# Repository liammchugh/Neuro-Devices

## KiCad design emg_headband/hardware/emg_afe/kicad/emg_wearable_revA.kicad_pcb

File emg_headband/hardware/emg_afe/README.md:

# EMG wearable, Rev A (KiCad, JLCPCB)

One to three channel surface EMG front end on a battery-powered headband
wearable, built around a TI ADS1298 and an ESP32-S3-MINI-1 module (placed by
JLCPCB, no hand soldering) that sends data to the
pedal wirelessly. The original discrete single-channel design (INA333 + OPA2333)
is in git history (commit 3aedaac) and in `../../docs/`.

Rev A is a bench board. Synthetic differential inputs first; no body electrodes
until the isolation checks in "Bring-up" pass.

## Requirements (reviewed, Liam, 11 Oct 2026)

1. Works with 1, 2 or 3 simultaneous electrode pairs, chosen by firmware mode,
   with no rework.
2. Electrodes: one 3.5 mm TRS jack for CH1 (tip +, ring −, sleeve REF) plus a
   1 mm FPC carrying CH1 to CH3 for flex-PCB arrays or a breakout (Liam, 11 Oct
   2026: three 3.5 mm jacks do not fit the 2.5" × 1" board). All REF sleeves share
   one reference/RLD net, so 9 electrodes (3 REF) or 7 (1 REF) both work.
   Series resistors on every input.
3. Power: passive USB/battery handling in every state (battery, USB, both), no
   switches. Dedicated low-noise analog rail. Protected LiPo.
4. Debug: USB serial over the board USB-C (ESP32-S3 native USB). The isolated UART footprint was
   dropped for size.
9. Board: 2-layer flex PCB, 62.5 × 25.4 mm (2.46" × 1"; limit 2.5" × 1"),
   ESP32-S3 module at one end with USB-C pointing down (across the long axis),
   jack and FPC at the other end. Everything JLC-assembled (Liam, 11 Oct 2026:
   chip on board instead of a XIAO, whose BAT pads are on its underside).
5. Filtering in firmware: capture wide (about 0.5 Hz up, 4 kSPS or more) so
   blink/EOG and envelope data are kept; 20 to 450 Hz is the EMG band.
6. Lead-off detection (built into the ADS1298).
7. JLCPCB assembly, LCSC parts, smallest practical size for a headband.
8. Pedal side is out of scope; it gets data wirelessly.

## Decisions

| Topic | Decision | Source |
|---|---|---|
| Architecture | Battery wearable, wireless to pedal (BLE / ESP-NOW). USB-C for flashing, charging and serial debug | Liam, 11 Oct 2026 |
| Front end | ADS1298 (8 ch, 24-bit, PGA, RLD, lead-off), CH1 to CH3 used, CH4 to CH8 tied to AVDD and powered down | Liam, 11 Oct 2026 |
| Sample rate | 4 kSPS (or 8 kSPS) from the ADS1298, decimate in firmware | Reviews |
| Filtering | Firmware: HPF about 0.5 Hz for wideband capture, 20 to 450 Hz for EMG features | Liam, 11 Oct 2026 |
| Input network | 22 kΩ series + 100 pF C0G to AGND per input (≈ 72 kHz; kept small for dry-electrode CMRR). The ADS1298 modulator runs at 512 kHz, so no higher-order anti-alias filter is needed | Datasheet |
| Reference / RLD | RLDOUT with 1 MΩ ∥ 1.5 nF feedback (datasheet), 330 kΩ series to the REF electrode(s), DC fault current < 10 µA | Datasheet, critic review |
| Schematic | Flat, one A3 sheet | Review 2 |

## Isolation and USB debug

The wearable is isolated from the pedal and mains by being battery powered and
wireless. The USB-C port is the one non-isolated path: when it is plugged
into a computer, the body would be connected through the reference electrode,
AGND and the USB shield to mains earth, and the guitar strings are on mains
earth too.

Rev A relies on one rule: **USB serial over the board's USB-C is the debug
path** (Liam, 11 Oct 2026), as on any Arduino-style R&D board. With electrodes
on the body and USB plugged in, run the laptop on battery and unplugged from
mains, or use a synthetic input instead of electrodes. This note is on the
schematic. A USB isolator dongle between the laptop and the board is the easy
upgrade when the laptop has to stay on mains.

The isolated UART footprint (ISO7721) from earlier drafts was dropped to fit
the 2.5" × 1" flex board.

Charging while worn: only from a battery-powered laptop or an isolated (Class II) USB charger.

## Circuit

**Power and reference**
- LiPo (protected cell) soldered to J3 (two SMD pads next to the USB-C).
  U8 MCP73831 charges it from USB at 100 mA (R703 = 10 kΩ; lower R703 for a
  bigger cell).
- Passive power path, no switches: USB 5 V through a Schottky (D101, B5819W)
  and the battery through a P-MOSFET (Q101, AO3401A, gate on VBUS with a 100 kΩ
  pull-down) join at `VSYS`. USB present: Q101 is off and VSYS ≈ 4.7 V from
  USB. USB absent: Q101 is on and VSYS = VBAT. Both: USB carries the load while
  U8 charges the battery.
- **On/off:** SW1 (MSK12C02 side slide switch, lever out of the bottom edge
  next to the filter block) sits between the battery and Q101. Off: the cell
  is fully disconnected from the system (0 µA); USB still powers the board and
  U8 still charges the cell. Slide toward the "ON" label to turn it on.
- **Battery monitor:** VBAT_SYS / 2 (1 MΩ / 1 MΩ, 100 nF) into IO10
  (ADC1_CH9); draws 2 µA only while on.
- **Charge LED:** D102 (red) from VBUS through 1 kΩ into the MCP73831 STAT
  pin; lit while charging, off when full or without USB.
- `+3V3` (ESP32-S3, ADS1298 DVDD) from U9 AP2112K-3.3 (600 mA) on VSYS.
- `+3V0_A` (ADS1298 AVDD) from a dedicated low-noise LDO (U6, LP5907MFX-3.0,
  6.5 µVrms, 82 dB PSRR at 1 kHz) on VSYS. EN is tied to `+3V3`, so the AFE is
  never live while the MCU rail is off. AVDD − DVDD = −0.3 V, inside the −2.1
  to 3.6 V limit.

**MCU and USB**
- U2 ESP32-S3-MINI-1-N8 (8 MB flash, PCB antenna at the board end; the
  antenna area is kept free of copper on both layers).
- J7 HRO TYPE-C-31-M-12 USB-C (5.1 kΩ CC pull-downs), USBLC6-2SC6 ESD, data
  to the ESP32-S3 native USB (IO19/IO20). Flashing and serial go through the
  built-in USB-Serial-JTAG, so no USB-UART chip or auto-reset circuit.
- EN: 10 kΩ / 1 µF RC. No buttons, to save space: if USB ever stops
  enumerating, short TP10 (IO0) to GND and tap TP9 (EN) to GND to force the
  ROM bootloader. Both pads are on the back.

**Electrodes**
- J1: CUI SJ-3523-SMT 3.5 mm TRS jack for CH1 (tip ELEC1_P, ring ELEC1_N,
  sleeve `RLD_ELEC`).
- J6: Hirose FH34SRJ-12S-0.5SH(50) back-flip FPC (C424659; 12 pins, 0.5 mm,
  1.0 mm tall), in parallel with J1 for CH1: use one or the other. CH2 and CH3 are on J6 only. Pinout: 1 AGND, 2/3 CH1 P/N, 4 REF, 5 AGND, 6/7 CH2 P/N, 8 REF, 9 AGND,
  10/11 CH3 P/N, 12 REF, MP AGND. Footprint `emg_wearable:Hirose_FH34SRJ-12S-0.5SH_...` is drawn from
  the Hirose land pattern; check it against the datasheet before ordering. The
  FPC inserts from the mounting-tab side, which faces the board edge; the
  signal pads and back-flip actuator are on the inboard side.

**ADS1298 (U1)**
- IN1 to IN3 from the input RC (22 kΩ + 100 pF C0G). IN4 to IN8 and TESTP_PACE_OUT1/2 to AVDD, as
  the datasheet asks for unused analog pins.
- Internal 2.4 V reference: VREFP 10 µF + 100 nF to AGND, VREFN to AGND.
- VCAP1 22 µF, VCAP2/3/4 1 µF to AGND. AVDD 10 µF + 2× 100 nF, DVDD 1 µF +
  100 nF.
- Internal clock (CLKSEL high, CLK not connected). RESV1 and DAISY_IN to DGND.
  RLDREF and WCT not connected (internal mid-supply reference). GPIO1 to 4 not
  connected: set them as outputs in firmware.
- RLDIN tied to `RLD_ELEC` so firmware can measure the REF electrode.
- SPI to the ESP32-S3: IO12 SCLK, IO13 DOUT (MISO), IO14 DIN (MOSI), IO15 CS
  (10 k pull-up), IO16 DRDY, IO17 START, IO18 RESET (10 k pull-up). PWDN held
  high by 10 k; use register standby instead. Strapping pins (IO0, IO3, IO45,
  IO46) are not used.
- Firmware: power down unused channels (CHnSET.PDn), pick RLD sense channels
  (RLD_SENSP/N) and use lead-off (LOFF) to detect which electrodes are attached.

## BOM notes for JLCPCB

| Part | LCSC | Note |
|---|---|---|
| ADS1298IPAGR | C527440 | extended, ≈ $20, 1,953 in stock on 11 Oct 2026 |
| LP5907MFX-3.0/NOPB | C475492 | extended |
| ESP32-S3-MINI-1-N8 | C2913206 | extended, footprint from the CERN library (CERN-OHL-P-2.0) |
| TYPE-C-31-M-12 | C165948 | extended, has through-hole shell tabs |
| MCP73831T-2ACI/OT, AP2112K-3.3TRG1, USBLC6-2SC6 | C424093, C51118, C7519 | extended |
| AO3401A, B5819W | C15127, C8598 | basic |
| SJ-3523-SMT-TR | C4991872 | extended, 737 in stock; PJ-320D (C431535) is a fallback with a different footprint |
| FH34SRJ-12S-0.5SH(50) | C424659 | extended, 1 mm tall, custom footprint |

Every JLC-placed symbol in `kicad/emg_wearable_revA.kicad_sch` carries an
`LCSC` field; the grouped BOM is in `kicad/bom/`. Only the LiPo leads are
hand-soldered.

## Board

2-layer flex (polyimide), 62.5 × 25.4 mm (2.46" × 1"), parts on top, test pads on the back. Layout notes:

- ESP32-S3 module at the left with its antenna at the board end, USB-C on the
  bottom edge (points down the spine), charger and LiPo pads beside the USB-C,
  then a column with the 3.3 V and 3.0 V regulators, power path and pull-ups.
- ADS1298 in the middle with its decoupling caps above and below. J1 jack at
  the top right (plug toward the end), J6 FPC at the bottom right with its
  opening on the board edge, and the input RC filters right next to J6.
- Test pads (rails, VSYS, RLD_OUT, AGND) are on the back, under the input RC
  block where there is no stiffener.
- AGND pours on both layers with stitching vias. Routed with Freerouting, then
  checked in KiCad: DRC is clean apart from the J1 silkscreen running over the
  board edge where the jack overhangs.
- Stiffeners (0.2 mm FR4, back side) are drawn on the `Stiffener` (User.1)
  layer: under the ESP32-S3 module and USB-C, under the ADS1298 block and
  under J1/J6. The power
  column and the input RC block are the bend zones; keep bends there gentle
  since they carry 0603 parts.

Fab outputs are in `kicad/fab/`: gerbers and drill files, `*_bom_jlc.csv` and
`*_cpl_jlc.csv` for JLCPCB assembly. The LiPo pads and test points are
excluded from assembly. Check part rotations in JLC's placement preview
(SOT-23, SOT-23-5, TQFP, the ESP32 module and the USB-C often need an offset).

## Bring-up

Full staged plan with pass/fail values: [BRINGUP_revA.md](BRINGUP_revA.md). Firmware:
[`../../firmware/revA_bringup`](../../firmware/revA_bringup/README.md).

1. No electrodes. Check VSYS on battery, USB and both; `+3V0_A`; idle current.
2. Read the ADS1298 ID register, run its internal test signal and input-short
   noise test on each channel.
3. Synthetic 1 mVpp differential input, sweep 1 Hz to 2 kHz, one to three
   channels at a time.
4. 50/60 Hz common-mode test with mismatched source impedances, RLD on and off.
5. Confirm no continuity between electrode nets and the debug header's computer
   side.
6. Only then electrodes, on battery or a battery-powered laptop.

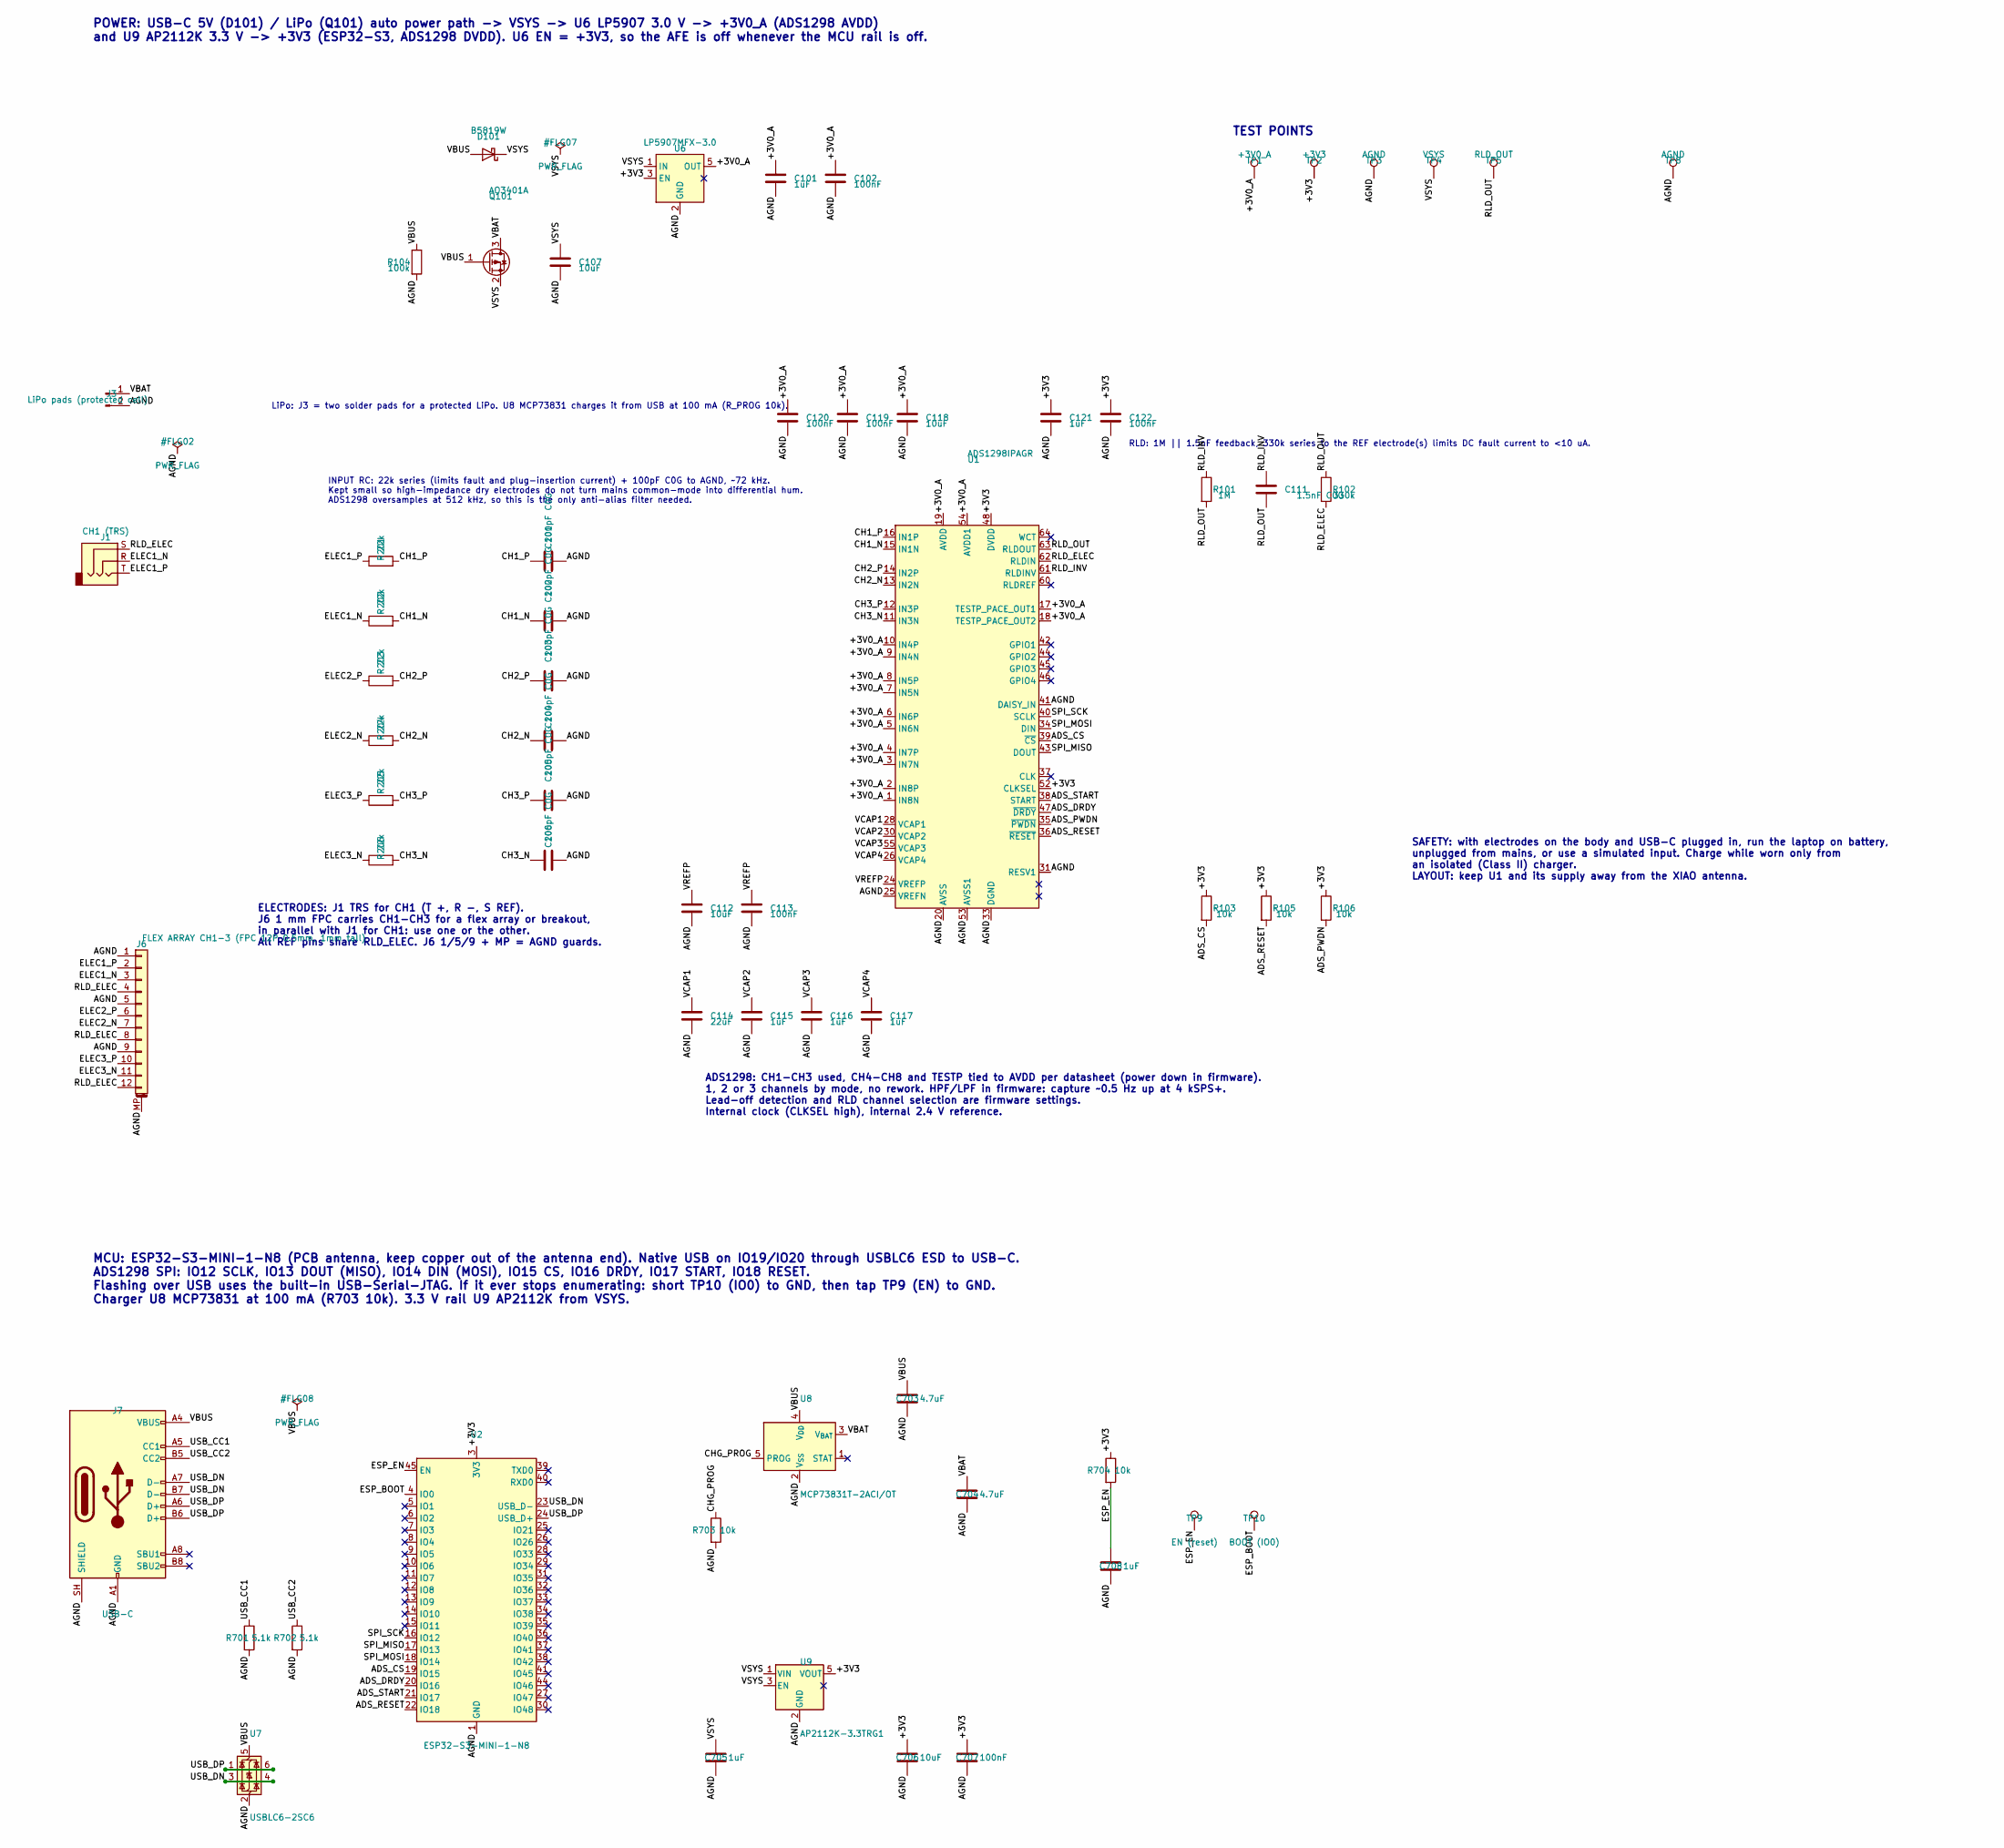
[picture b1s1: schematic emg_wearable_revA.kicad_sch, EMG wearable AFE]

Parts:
C101, C115, C116, C117, C121, C705, C708: 1uF; C_0603_1608Metric; LCSC C15849
C102, C113, C119, C120, C122, C707: 100nF; C_0603_1608Metric; LCSC C14663
C107, C112, C118, C706: 10uF; C_0603_1608Metric; LCSC C19702
C111: 1.5nF C0G; C_0603_1608Metric; LCSC C162204
C114: 22uF; C_0603_1608Metric; LCSC C59461
C201, C202, C203, C204, C205, C206: 100pF C0G; C_0603_1608Metric; LCSC C14858
C703, C704: 4.7uF; C_0603_1608Metric; LCSC C19666
D101: B5819W; D_SOD-123; LCSC C8598
J1: CH1 (TRS); Jack_3.5mm_CUI_SJ-3523-SMT_Horizontal; MPN CUI SJ-3523-SMT-TR; LCSC C4991872
J3: LiPo pads (protected cell); LiPo_SolderPads_2x1.5x2.5mm_P2.6mm
J6: FLEX ARRAY CH1-3 (FPC 12P 0.5mm, 1mm tall); Hirose_FH34SRJ-12S-0.5SH_1x12-1MP_P0.50mm_Horizontal; MPN Hirose FH34SRJ-12S-0.5SH(50); LCSC C424659
J7: USB-C; USB_C_Receptacle_HRO_TYPE-C-31-M-12; MPN HRO TYPE-C-31-M-12; LCSC C165948
Q101: AO3401A; SOT-23; LCSC C15127
R101: 1M; R_0603_1608Metric; LCSC C22935
R102: 330k; R_0603_1608Metric; LCSC C23137
R103, R105, R106, R703, R704: 10k; R_0603_1608Metric; LCSC C25804
R104: 100k; R_0603_1608Metric; LCSC C25803
R201, R202, R203, R204, R205, R206: 22k; R_0603_1608Metric; LCSC C31850
R701, R702: 5.1k; R_0603_1608Metric; LCSC C23186
TP1: +3V0_A; TestPoint_Pad_D1.0mm
TP2: +3V3; TestPoint_Pad_D1.0mm
TP3, TP8: AGND; TestPoint_Pad_D1.0mm
TP4: VSYS; TestPoint_Pad_D1.0mm
TP5: RLD_OUT; TestPoint_Pad_D1.0mm
TP9: EN (reset); TestPoint_Pad_D1.0mm
TP10: BOOT (IO0); TestPoint_Pad_D1.0mm
U1: ADS1298IPAGR; TQFP-64_10x10mm_P0.5mm; LCSC C527440
U2: ESP32-S3-MINI-1-N8; ESP32-S3-MINI-1; LCSC C2913206
U6: LP5907MFX-3.0; SOT-23-5; LCSC C475492
U7: USBLC6-2SC6; SOT-23-6; LCSC C7519
U8: MCP73831T-2ACI/OT; SOT-23-5; LCSC C424093
U9: AP2112K-3.3TRG1; SOT-23-5; LCSC C51118

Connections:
+3V0_A: C101.1, C102.1, C118.1, C119.1, C120.1, TP1.1, U1.1 (IN8N), U1.2 (IN8P), U1.3 (IN7N), U1.4 (IN7P), U1.5 (IN6N), U1.6 (IN6P), U1.7 (IN5N), U1.8 (IN5P), U1.9 (IN4N), U1.10 (IN4P), U1.17 (TESTP_PACE_OUT1), U1.18 (TESTP_PACE_OUT2), U1.19 (AVDD), U1.21 (AVDD), U1.22 (AVDD), U1.54 (AVDD1), U1.56 (AVDD), U1.59 (AVDD), U6.5 (OUT)
+3V3: C121.1, C122.1, C706.1, C707.1, R103.1, R105.1, R106.1, R704.1, TP2.1, U1.48 (DVDD), U1.50 (DVDD), U1.52 (CLKSEL), U2.3 (3V3), U6.3 (EN), U9.5 (VOUT)
ADS_CS: R103.2, U1.39 (~CS), U2.19 (IO15)
ADS_DRDY: U1.47 (~DRDY), U2.20 (IO16)
ADS_PWDN: R106.2, U1.35 (~PWDN)
ADS_RESET: R105.2, U1.36 (~RESET), U2.22 (IO18)
ADS_START: U1.38 (START), U2.21 (IO17)
AGND: C101.2, C102.2, C107.2, C112.2, C113.2, C114.2, C115.2, C116.2, C117.2, C118.2, C119.2, C120.2, C121.2, C122.2, C201.2, C202.2, C203.2, C204.2, C205.2, C206.2, C703.2, C704.2, C705.2, C706.2, C707.2, C708.2, J3.2, J6.1, J6.5, J6.9, J6.MP (MountPin), J7.A1 (GND), J7.A12 (GND), J7.B1 (GND), J7.B12 (GND), J7.SH (SHIELD), R104.2, R701.2, R702.2, R703.2, TP3.1, TP8.1, U1.20 (AVSS), U1.23 (AVSS), U1.25 (VREFN), U1.31 (RESV1), U1.32 (AVSS), U1.33 (DGND), U1.41 (DAISY_IN), U1.49 (DGND), U1.51 (DGND), U1.53 (AVSS1), U1.57 (AVSS), U1.58 (AVSS), U2.1 (GND), U2.2 (GND), U2.42 (GND), U2.43 (GND), U2.46 (GND), U2.47 (GND), U2.48 (GND), U2.49 (GND), U2.50 (GND), U2.51 (GND), U2.52 (GND), U2.53 (GND), U2.54 (GND), U2.55 (GND), U2.56 (GND), U2.57 (GND), U2.58 (GND), U2.59 (GND), U2.60 (GND), U2.61 (GND), U2.62 (GND), U2.63 (GND), U2.64 (GND), U2.65 (GND), U6.2 (GND), U7.2 (GND), U8.2 (V_{SS}), U9.2 (GND); also elsewhere on the board
CH1_N: C202.1, R202.2, U1.15 (IN1N)
CH1_P: C201.1, R201.2, U1.16 (IN1P)
CH2_N: C204.1, R204.2, U1.13 (IN2N)
CH2_P: C203.1, R203.2, U1.14 (IN2P)
CH3_N: C206.1, R206.2, U1.11 (IN3N)
CH3_P: C205.1, R205.2, U1.12 (IN3P)
CHG_PROG: R703.1, U8.5 (PROG)
CHG_STAT: U8.1 (STAT); also elsewhere on the board
ELEC1_N: J1.R, J6.3, R202.1
ELEC1_P: J1.T, J6.2, R201.1
ELEC2_N: J6.7, R204.1
ELEC2_P: J6.6, R203.1
ELEC3_N: J6.11, R206.1
ELEC3_P: J6.10, R205.1
ESP_BOOT: TP10.1, U2.4 (IO0)
ESP_EN: C708.1, R704.2, TP9.1, U2.45 (EN)
RLD_ELEC: J1.S, J6.4, J6.8, J6.12, R102.2, U1.62 (RLDIN)
RLD_INV: C111.1, R101.1, U1.61 (RLDINV)
RLD_OUT: C111.2, R101.2, R102.1, TP5.1, U1.63 (RLDOUT)
SPI_MISO: U1.43 (DOUT), U2.17 (IO13)
SPI_MOSI: U1.34 (DIN), U2.18 (IO14)
SPI_SCK: U1.40 (SCLK), U2.16 (IO12)
USB_CC1: J7.A5 (CC1), R701.1
USB_CC2: J7.B5 (CC2), R702.1
USB_DN: J7.A7 (D-), J7.B7 (D-), U2.23 (USB_D-), U7.3 (I/O2), U7.4 (I/O2)
USB_DP: J7.A6 (D+), J7.B6 (D+), U2.24 (USB_D+), U7.1 (I/O1), U7.6 (I/O1)
VBAT_SENSE: U2.14 (IO10); also elsewhere on the board
VBUS: C703.1, D101.2 (A), J7.A4 (VBUS), J7.A9 (VBUS), J7.B4 (VBUS), J7.B9 (VBUS), Q101.1 (G), R104.1, U7.5 (VBUS), U8.4 (V_{DD}); also elsewhere on the board
VCAP1: C114.1, U1.28 (VCAP1)
VCAP2: C115.1, U1.30 (VCAP2)
VCAP3: C116.1, U1.55 (VCAP3)
VCAP4: C117.1, U1.26 (VCAP4)
VREFP: C112.1, C113.1, U1.24 (VREFP)
VSYS: C107.1, C705.1, D101.1 (K), Q101.2 (S), TP4.1, U6.1 (IN), U9.1 (VIN), U9.3 (EN)

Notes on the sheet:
POWER: USB-C 5V (D101) / LiPo (Q101) auto power path -> VSYS -> U6 LP5907 3.0 V -> +3V0_A (ADS1298 AVDD) and U9 AP2112K 3.3 V -> +3V3 (ESP32-S3, ADS1298 DVDD). U6 EN = +3V3, so the AFE is off whenever the MCU rail is off.
ELECTRODES: J1 TRS for CH1 (T +, R -, S REF). J6 1 mm FPC carries CH1-CH3 for a flex array or breakout, in parallel with J1 for CH1: use one or the other. All REF pins share RLD_ELEC. J6 1/5/9 + MP = AGND guards.
INPUT RC: 22k series (limits fault and plug-insertion current) + 100pF C0G to AGND, ~72 kHz. Kept small so high-impedance dry electrodes do not turn mains common-mode into differential hum. ADS1298 oversamples at 512 kHz, so this is the only anti-alias filter needed.
ADS1298: CH1-CH3 used, CH4-CH8 and TESTP tied to AVDD per datasheet (power down in firmware). 1, 2 or 3 channels by mode, no rework. HPF/LPF in firmware: capture ~0.5 Hz up at 4 kSPS+. Lead-off detection and RLD channel selection are firmware settings. Internal clock (CLKSEL high), internal 2.4 V r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
RLD: 1M || 1.5nF feedback, 330k series to the REF electrode(s) limits DC fault current to <10 uA.
SAFETY: with electrodes on the body and USB-C plugged in, run the laptop on battery, unplugged from mains, or use a simulated input. Charge while worn only from an isolated (Class II) charger. LAYOUT: keep U1 and its supply away from the XIAO antenna.
LiPo: J3 = two solder pads for a protected LiPo. U8 MCP73831 charges it from USB at 100 mA (R_PROG 10k).
TEST POINTS
MCU: ESP32-S3-MINI-1-N8 (PCB antenna, keep copper out of the antenna end). Native USB on IO19/IO20 through USBLC6 ESD to USB-C. ADS1298 SPI: IO12 SCLK, IO13 DOUT (MISO), IO14 DIN (MOSI), IO15 CS, IO16 DRDY, IO17 START, IO18 RESET. Flashing over USB uses the built-in USB-Serial-JTAG. If it ever stop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

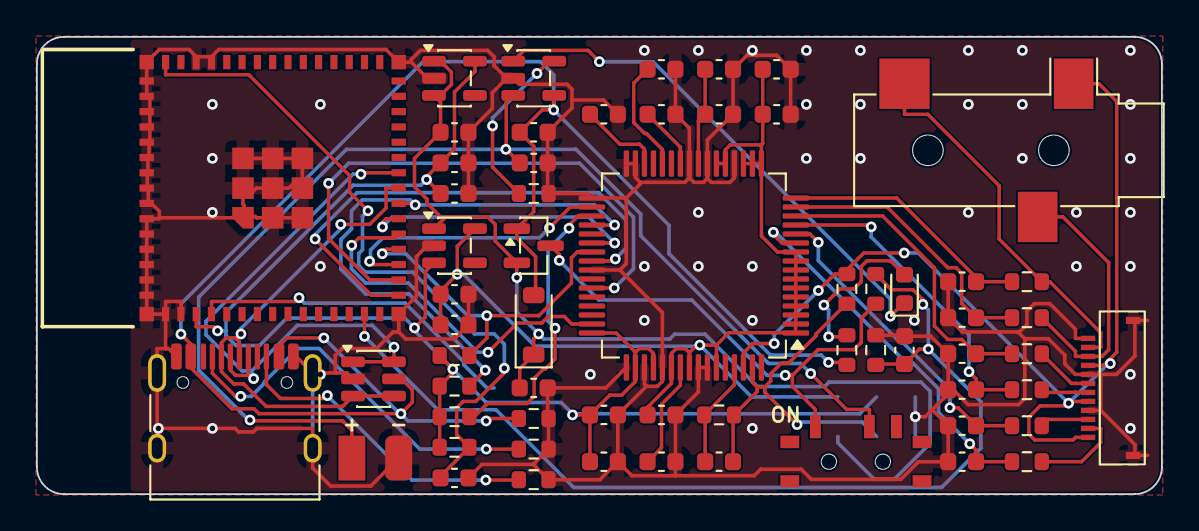
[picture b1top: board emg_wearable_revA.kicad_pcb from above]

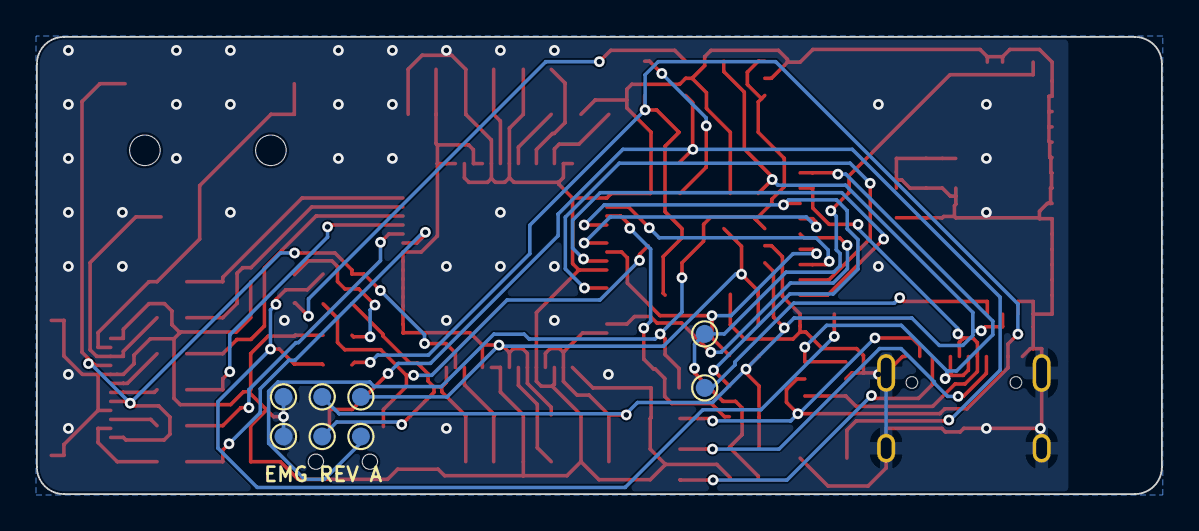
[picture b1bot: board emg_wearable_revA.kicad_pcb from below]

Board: 2 copper layers, 62.5 x 25.4 mm, 69 parts (8 on the bottom side), 45 nets.

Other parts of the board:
C709: 100nF; C_0603_1608Metric
D102: CHG red; LED_0603_1608Metric
R705, R706: 1M; R_0603_1608Metric
R707: 1k; R_0603_1608Metric
SW1: PWR (MSK12C02); SW_SPDT_Slide_SHOUHAN_MSK12C02

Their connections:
AGND: C709.2, R706.2; also elsewhere on the board
CHG_LED: D102.2, R707.2
CHG_STAT: D102.1; also elsewhere on the board
VBAT_SENSE: C709.1, R705.2, R706.1; also elsewhere on the board
VBUS: R707.1; also elsewhere on the board

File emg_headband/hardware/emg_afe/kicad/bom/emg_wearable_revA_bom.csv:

"Designator","Value","Footprint","LCSC","Qty","DNP"
"C101,C115,C116,C117,C121,C705,C708","1uF","Capacitor_SMD:C_0603_1608Metric","C15849","7",""
"C102,C113,C119,C120,C122,C707,C709","100nF","Capacitor_SMD:C_0603_1608Metric","C14663","7",""
"C107,C112,C118,C706","10uF","Capacitor_SMD:C_0603_1608Metric","C19702","4",""
"C111","1.5nF C0G","Capacitor_SMD:C_0603_1608Metric","C162204","1",""
"C114","22uF","Capacitor_SMD:C_0603_1608Metric","C59461","1",""
"C201,C202,C203,C204,C205,C206","100pF C0G","Capacitor_SMD:C_0603_1608Metric","C14858","6",""
"C703,C704","4.7uF","Capacitor_SMD:C_0603_1608Metric","C19666","2",""
"D101","B5819W","Diode_SMD:D_SOD-123","C8598","1",""
"D102","CHG red","LED_SMD:LED_0603_1608Metric","C2286","1",""
"J1","CH1 (TRS)","Connector_Audio:Jack_3.5mm_CUI_SJ-3523-SMT_Horizontal","C4991872","1",""
"J3","LiPo pads (protected cell)","emg_wearable:LiPo_SolderPads_2x1.5x2.5mm_P2.6mm","","1",""
"J6","FLEX ARRAY CH1-3 (FPC 12P 0.5mm, 1mm tall)","emg_wearable:Hirose_FH34SRJ-12S-0.5SH_1x12-1MP_P0.50mm_Horizontal","C424659","1",""
"J7","USB-C","Connector_USB:USB_C_Receptacle_HRO_TYPE-C-31-M-12","C165948","1",""
"Q101","AO3401A","Package_TO_SOT_SMD:SOT-23","C15127","1",""
"R101,R705,R706","1M","Resistor_SMD:R_0603_1608Metric","C22935","3",""
"R102","330k","Resistor_SMD:R_0603_1608Metric","C23137","1",""
"R103,R105,R106,R703,R704","10k","Resistor_SMD:R_0603_1608Metric","C25804","5",""
"R104","100k","Resistor_SMD:R_0603_1608Metric","C25803","1",""
"R201,R202,R203,R204,R205,R206","22k","Resistor_SMD:R_0603_1608Metric","C31850","6",""
"R701,R702","5.1k","Resistor_SMD:R_0603_1608Metric","C23186","2",""
"R707","1k","Resistor_SMD:R_0603_1608Metric","C21190","1",""
"SW1","PWR (MSK12C02)","emg_wearable:SW_SPDT_Slide_SHOUHAN_MSK12C02","C431540","1",""
"TP1","+3V0_A","TestPoint:TestPoint_Pad_D1.0mm","","1",""
"TP2","+3V3","TestPoint:TestPoint_Pad_D1.0mm","","1",""
"TP3,TP8","AGND","TestPoint:TestPoint_Pad_D1.0mm","","2",""
"TP4","VSYS","TestPoint:TestPoint_Pad_D1.0mm","","1",""
"TP5","RLD_OUT","TestPoint:TestPoint_Pad_D1.0mm","","1",""
"TP9","EN (reset)","TestPoint:TestPoint_Pad_D1.0mm","","1",""
"TP10","BOOT (IO0)","TestPoint:TestPoint_Pad_D1.0mm","","1",""
"U1","ADS1298IPAGR","Package_QFP:TQFP-64_10x10mm_P0.5mm","C527440","1",""
"U2","ESP32-S3-MINI-1-N8","emg_wearable:ESP32-S3-MINI-1","C2913206","1",""
"U6","LP5907MFX-3.0","Package_TO_SOT_SMD:SOT-23-5","C475492","1",""
"U7","USBLC6-2SC6","Package_TO_SOT_SMD:SOT-23-6","C7519","1",""
"U8","MCP73831T-2ACI/OT","Package_TO_SOT_SMD:SOT-23-5","C424093","1",""
"U9","AP2112K-3.3TRG1","Package_TO_SOT_SMD:SOT-23-5","C51118","1",""

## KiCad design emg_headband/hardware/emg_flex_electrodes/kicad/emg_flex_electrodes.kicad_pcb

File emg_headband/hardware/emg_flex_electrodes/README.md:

# Forehead EMG electrode flex, Rev A draft

A single 2-layer polyimide flex that carries seven skin electrodes across the
forehead and temple and runs back above the right ear to the main board's FPC
connector (J6, Hirose FH34SRJ-12S-0.5SH) at the back of the head.

Status: draft for discussion. DRC is clean in KiCad 7 (0 violations, 0
unconnected, zones filled); the board has not been fitted on a head yet.

## Files

Everything is generated by `gen_flex.py` (`pip install shapely matplotlib`):
edit the constants at the top (electrode sites, tail side and length, pin
order, ear keep-out) and re-run. Don't edit the KiCad files by hand; changes
would be lost on the next run.

- `kicad/emg_flex_electrodes.kicad_pro`: the KiCad project. Open this.
- `kicad/emg_flex_electrodes.kicad_sch`: schematic, 7 electrodes and the
  12-contact tail, connected by net labels. Its symbol UUIDs match the board's
  footprints, so "Update PCB from Schematic" finds no changes.
- `kicad/emg_flex_electrodes.kicad_pcb`: the routed board. Zones are saved
  unfilled: press **B** after opening.
- `kicad/emg_flex.kicad_sym`, `kicad/emg_flex.pretty/`: project symbol and
  footprint libraries (electrode domes 8 and 12 mm, FPC tail), wired up through
  the project's `sym-lib-table` and `fp-lib-table`.
- `kicad/emg_flex_electrodes.kicad_dru`: lets the FPC contacts sit 0.2 mm from
  the tab edge.
- `docs/flex_layout.png`: drawing of the outline, electrodes, routing and ear.

Checks (KiCad 7 command-line and Python API): DRC clean with zones filled (0
violations, 0 unconnected); the schematic netlist matches every board pad's
net and footprint. Files are written in KiCad 7 format and open in KiCad 9/10,
which upgrade them on save.

## Ear clearance

The ear is modelled as an ellipse 120 to 184 mm along the band from the
forehead midline, with the top of the helix 8 mm above the brow line (it is
usually at or below brow level, so this is conservative). The generator
refuses to write a board that comes within 12 mm of it; the current layout
clears it by 21 mm. The crossover block steps up to 26 mm above the brow
before the ear, and the tail runs 30 to 38 mm above the brow over it, which
also keeps it clear of glasses arms. The ear outline and keep-out are drawn on
the board's `User.Drawings` layer.

## Electrode sites

Coordinates are arc length along the band from the forehead midline (+ toward
the tail, which runs along the subject's right) and height above the eyebrow
line. The tail side is `TAIL_SIDE` in `gen_flex.py`; it follows the main
board's connector (see below).

| Electrode | Net | Site (x, y) mm | Muscle and gesture | Pair axis |
|---|---|---|---|---|
| E1 / E2 | CH1 +/- | (30, 34) / (30, 14) | Right frontalis, above mid-pupil: brow raise | Vertical, along the fibres, 20 mm |
| E3 / E4 | CH2 +/- | (-10, 8) / (-25, 8) | Left corrugator, just above the inner brow: frown | Horizontal, along the fibres, 15 mm |
| E5 / E6 | CH3 +/- | (85, 34) / (85, 14) | Right anterior temporalis at the temple: jaw clench | Vertical, along the anterior fibres, 20 mm |
| E7 | REF / RLD | (0, 37) | Upper midline forehead, between the frontalis bellies | Ø12 mm for lower contact impedance |

Why these three:

- They give three gestures a player can make independently while playing:
  raise brows, frown, clench. Brow raise is the signal used in the earlier
  experiments (`signal_acquisition/data_2025-02-28_raisebrows.csv`).
- All three sit on skin a headband covers and that is usually free of hair.
  The temporalis site is at the front of the temple; on people with a low
  hairline it may sit on hair and need repositioning.
- Temporalis is how a headband gets "upper jaw" activity. The masseter is
  below the zygomatic arch and out of reach of a band; clench shows up
  strongly on anterior temporalis anyway.
- One side per muscle is enough because these gestures are bilateral. The
  corrugator pair is on the left and frontalis on the right to put distance
  between them. Expect crosstalk anyway: corrugator and the lower frontalis
  overlap at the brow, so firmware should treat CH1/CH2 as a mixed pair.
- REF at the upper midline sits over the thin aponeurosis between the two
  frontalis bellies, the quietest skin on the forehead.

Spacing follows SENIAM: 20 mm between electrode centres, along the fibre
direction. Corrugator is a small muscle, so its pair is at 15 mm. Pads are
Ø8 mm.

## Construction

- 2-layer polyimide, 0.11 mm, ENIG, yellow or black coverlay (JLCPCB flex).
  The outline is 298 × 43 mm, inside JLC's 234 × 490 mm flex limit.
- Skin side is **B**. Electrodes are Ø8 mm (REF Ø12) ENIG pads exposed on B,
  with a 2.7 mm plated hole for an optional domed rivet soldered on the outer
  (F) side.
- Signals run on **F** (outer). **B** carries a hatched shield between the
  traces and the skin, so traces do not pick up the skin they cross and the
  band stays flexible. The shield is tied to **REF**, not AGND (see "Copper
  and noise" below). The main board's AGND pins (1, 5, 9) are left
  unconnected on the flex.
- Along the tail the conductors keep the connector order at 0.5 mm pitch, so
  each P/N pair stays adjacent (small loop area), with a REF conductor between
  channels. A crossover block in front of the ear re-orders them with short
  B.Cu jumps so every electrode can leave the bundle without crossings.
- The three REF pins are joined into one REF net at the crossover.
- Stiffener (drawn on the `Stiffener` user layer, exported as
  `fab/*-Stiffener.gbr`): 0.2 mm PI on the B side of the FPC tab, giving
  about 0.31 mm with the 0.11 mm flex (Hirose asks for 0.30 ± 0.03 mm). Rev 1
  has no stiffeners at the electrodes; the foam disc behind each lobe supports
  the rivet. Add FR4 rings there in rev 2 if pads start to lift.

## Electrodes

Rev 1 needs no custom parts. Each site is an ENIG pad (Ø8 mm, REF Ø12 mm)
with a 2.7 mm plated hole, and works two ways:

1. **Flat pad (default, nothing to buy).** The gold pad is the electrode.
   On the hairless forehead this is enough electrically; what matters is
   steady pressure, so put a 2 to 3 mm closed-cell foam disc behind each
   electrode lobe (between flex and band). Many forehead headbands use flat
   contacts this way.
2. **Domed rivet (Liam's pick for rev 1).** A standard DIN 660 / ISO 1051
   round-head solid rivet, 2.5 × 3 mm, in copper: head Ø4.4 mm, 1.5 mm
   tall, a ready-made dome. Push it through the hole from the skin side, trim
   the shank flush to about 1 mm and solder it to the pad on the outer side
   (a hot iron; the rivet sinks heat). Copper solders easily and is skin-safe;
   it tarnishes, so wipe it before use or tin the head. The 3 mm size
   (Ø5.2 × 1.8 mm head) needs `DRILL = 3.1` in `gen_flex.py`.

Other stock options, not recommended for rev 1:

- SMD pogo pins (e.g. YIYUAN YTC1P-2010-01, LCSC C5221287, 2 mm, 3 mm tall):
  push through hair but have a small, pointed contact.
- A male ECG snap stud, to use stick-on gel electrodes when validating sites.

Bar ("wedge") electrodes like Delsys's are not sold as parts; they would be
custom. A custom silver dome (Ø6 mm, 1.2 mm tall, Ø1.4 mm shank) remains the
rev 2 upgrade if the rivets work but feel too sharp.

Dry contacts improve once the skin is a little moist; expect higher impedance
and more motion artefact in the first minutes.

## Copper and noise

Checked against the main board's input network (hardware/emg-rev-a-kicad
93eab72: 22 kΩ series + 100 pF C0G per input, RLD through 330 kΩ) and its
review notes on dry-electrode CMRR.

- **Width and thickness are not a noise problem.** The longest trace (CH2−,
  about 320 mm of 0.25 mm × 12 µm copper) is under 4 Ω. Its thermal noise is
  0.25 nV/√Hz, against 19 nV/√Hz from each 22 kΩ series resistor and far more
  from dry electrodes. The currents are nA (lead-off) to < 10 µA (RLD), so IR
  drop is nil. Wider or thicker copper would only add capacitance and make the
  flex stiffer; 1/3 oz is the better choice for a flex that bends.
- **Capacitance is what matters.** Each signal trace has roughly 35 to 55 pF
  to the hatched shield under it (0.17 pF/mm, estimated for a 25 µm polyimide
  core and 41 % hatch coverage). If the shield were AGND, that would sit in
  parallel with the main board's 100 pF input caps, which were cut from 1 nF
  for dry-electrode CMRR, and add 35 to 55 % back. With the shield at REF
  (the RLD-driven body potential) that capacitance carries no 50/60 Hz common
  mode, so it does not convert mains into a differential error.
- **What the shield capacitance still does:** with a 1 MΩ dry electrode it
  forms a low-pass at about 3 to 4 kHz, above the 20 to 450 Hz EMG band
  (under 2 % loss at 450 Hz).
- **P/N matching:** each pair's two traces run side by side and differ in
  length by at most 14 mm (CH2, whose electrodes sit 15 mm apart), about 2 pF.

## Ordering at JLCPCB

Upload `kicad/fab/emg_flex_electrodes_gerbers.zip` (gerbers, Excellon drill,
stiffener layer) and choose:

| Option | Value |
|---|---|
| Base material | Flex |
| Layers | 2 |
| Size | 303 × 43 mm (detected from the outline) |
| Thickness | 0.11 mm |
| Copper | 1/3 oz (0.25 mm tracks and gaps) |
| Coverlay | Yellow |
| Surface finish | ENIG, 1 µ" |
| Stiffener | Polyimide, 0.2 mm, one area: the FPC tab on the back (B) side, as drawn in the Stiffener gerber |
| Assembly | None (rivets and foam are fitted by hand) |

The board has 7 electrode pads with 2.7 mm plated holes, 0.3 mm vias and
0.25 mm tracks, all within JLC's regular flex rules. Before ordering, check the
tab against the Hirose FPC drawing and the main board's J6 orientation (below).

Rivets: DIN 660 round head, copper, 2.5 × 3 mm (head Ø4.4 × 1.5 mm), one per
electrode, 7 per board.

## Mating with the main board

The tail carries the main board's J6 pin order (hardware/emg-rev-a-kicad,
commit c72bb90, rechecked at 825610d): 1 AGND, 2/3 CH1 P/N, 4 REF, 5 AGND,
6/7 CH2 P/N, 8 REF, 9 AGND, 10/11 CH3 P/N, 12 REF. The AGND pins are not
connected on the flex. The tab is 6.5 mm wide with 0.3 × 2.5 mm contacts
at 0.5 mm pitch. The crossover block re-orders lanes, so a later pin order
change on the main board only means editing `PINS` and regenerating.

J6 sits on the main board's F side at its right edge, rotated so the FPC
enters from the right (mounting-tab side) with pin 1 toward the top of the
board. Assuming the main board is worn with F facing out and its USB-C
pointing down, that opening faces the subject's right, so the tail runs along
the right side. Seen from outside, the tail arrives with its outer side (F) up
and pin 1 at the top edge, which lands on J6 pin 1. The FH34SRJ makes contact
on either face of the FPC, so contacts on F work.

Check before ordering:

- **Main board orientation on the head.** If it is worn the other way up or
  with F facing the head, the tail must come from the other side or the pin
  order mirrors: set `TAIL_SIDE` or reverse `PINS` and regenerate.
- **Tail length.** `X_END` puts the tab end 270 mm along the band from the
  midline: half of Liam's 58 cm head (290 mm), minus about 27 mm from the back
  centre to J6's contacts on the 62.5 mm main board (c72bb90), plus about 7 mm
  slack.
  Recheck if the main board layout moves J6.
- **Elastic bands.** A flex does not stretch. If the band is elastic, fix the
  flex at the forehead and at the connector and leave slack (or a sewn S-loop)
  along the tail.
- **Tab and contacts** against the Hirose FH34SRJ FPC drawing (width G = 6.5
  ± 0.05 mm for 12 positions, thickness 0.30 ± 0.03 mm).

## Open questions

- Fit on a real head: brow-to-hairline height and where the band sits decide
  whether the 20 mm vertical pairs fit, or need to go to 15 mm.
- Whether a second temporalis pair (left side) is worth a channel; the
  ADS1298 has five spare channels but J6 only carries three.

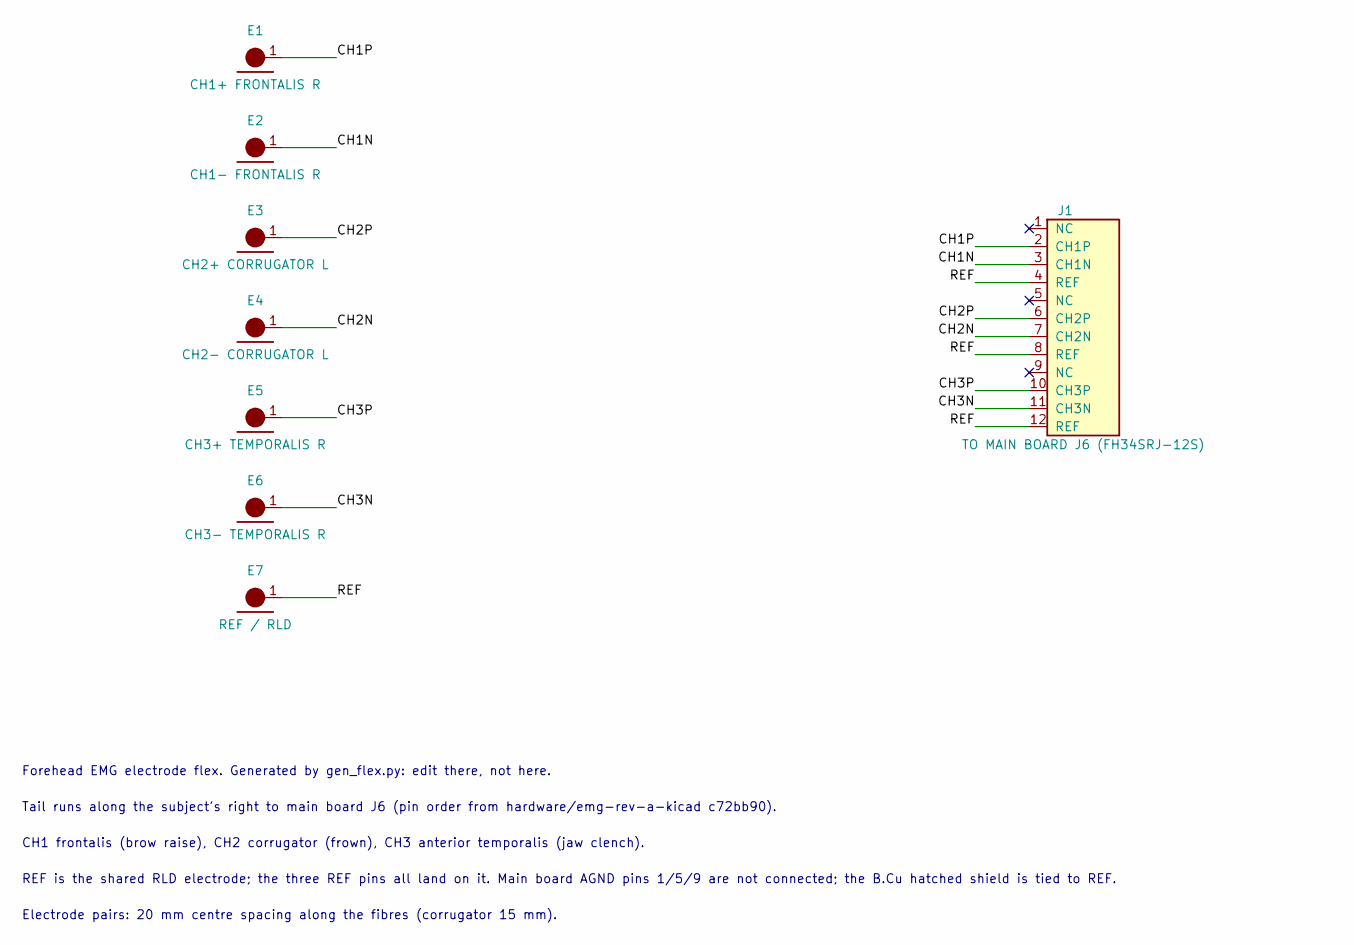
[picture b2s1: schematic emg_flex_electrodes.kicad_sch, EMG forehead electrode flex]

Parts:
E1: CH1+ FRONTALIS R; Electrode_Dome_8mm
E2: CH1- FRONTALIS R; Electrode_Dome_8mm
E3: CH2+ CORRUGATOR L; Electrode_Dome_8mm
E4: CH2- CORRUGATOR L; Electrode_Dome_8mm
E5: CH3+ TEMPORALIS R; Electrode_Dome_8mm
E6: CH3- TEMPORALIS R; Electrode_Dome_8mm
E7: REF / RLD; Electrode_Dome_12mm
J1: TO MAIN BOARD J6 (FH34SRJ-12S); FPC_Tail_12P_P0.50mm_FH34SRJ

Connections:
CH1N: E2.1, J1.3 (CH1N)
CH1P: E1.1, J1.2 (CH1P)
CH2N: E4.1, J1.7 (CH2N)
CH2P: E3.1, J1.6 (CH2P)
CH3N: E6.1, J1.11 (CH3N)
CH3P: E5.1, J1.10 (CH3P)
REF: E7.1, J1.4 (REF), J1.8 (REF), J1.12 (REF)

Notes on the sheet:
Forehead EMG electrode flex. Generated by gen_flex.py: edit there, not here.
Tail runs along the subject's right to main board J6 (pin order from hardware/emg-rev-a-kicad c72bb90).
CH1 frontalis (brow raise), CH2 corrugator (frown), CH3 anterior temporalis (jaw clench).
REF is the shared RLD electrode; the three REF pins all land on it. Main board AGND pins 1/5/9 are not connected; the B.Cu hatched shield is tied to REF.
Electrode pairs: 20 mm centre spacing along the fibres (corrugator 15 mm).

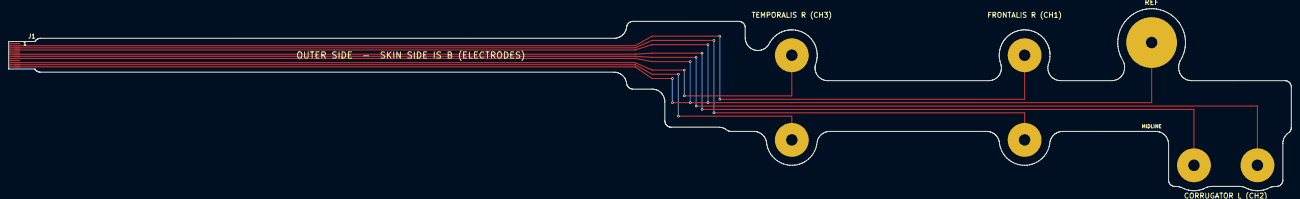
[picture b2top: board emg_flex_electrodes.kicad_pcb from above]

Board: 2 copper layers, 303.0 x 43.0 mm, 8 parts (0 on the bottom side), 7 nets.

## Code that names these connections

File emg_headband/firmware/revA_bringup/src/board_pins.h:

// Rev A pin map, read from emg_headband/hardware/emg_afe/kicad/emg_wearable_revA.kicad_pcb
// (U2 ESP32-S3-MINI-1 module pin -> net). Module pin N is GPIO(N-4) for pins 4..22.
#pragma once

constexpr int PIN_SPI_SCK   = 12;  // U2.16 SPI_SCK   -> U1.40 SCLK
constexpr int PIN_SPI_MISO  = 13;  // U2.17 SPI_MISO  -> U1.43 DOUT
constexpr int PIN_SPI_MOSI  = 14;  // U2.18 SPI_MOSI  -> U1.34 DIN
constexpr int PIN_ADS_CS    = 15;  // U2.19 ADS_CS    -> U1.39 CS     (R103 10k pull-up)
constexpr int PIN_ADS_DRDY  = 16;  // U2.20 ADS_DRDY  -> U1.47 DRDY
constexpr int PIN_ADS_START = 17;  // U2.21 ADS_START -> U1.38 START
constexpr int PIN_ADS_RESET = 18;  // U2.22 ADS_RESET -> U1.36 RESET  (R105 10k pull-up)
constexpr int PIN_VBAT_SENSE = 10; // U2.14 VBAT_SENSE, VBAT_SYS / 2 (R705/R706 1M/1M, C709)
// ADS1298 PWDN is held high by R106 (no GPIO). IO0 = TP10 (BOOT), EN = TP9.
// USB D-/D+ on IO19/IO20 (native USB).

constexpr float VBAT_DIVIDER = 2.0f;

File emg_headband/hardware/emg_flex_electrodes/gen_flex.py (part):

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
# --- Connector (main board J6, Hirose FH34SRJ-12S-0.5SH, 0.5 mm pitch) -------
# Pin order as on hardware/emg-rev-a-kicad (commit c72bb90, 11 Oct 2026).
PINS = {1: "AGND", 2: "CH1P", 3: "CH1N", 4: "REF", 5: "AGND", 6: "CH2P",
        7: "CH2N", 8: "REF", 9: "AGND", 10: "CH3P", 11: "CH3N", 12: "REF"}
# The main board's AGND pins (1, 5, 9) are left unconnected on the flex. The
# B.Cu shield is tied to REF instead: REF is the RLD-driven body potential, so
# the ~35-55 pF each signal trace has to the shield carries no common-mode
# current and does not convert 50/60 Hz into a differential error. An AGND
# shield would add that capacitance to AGND on top of the main board's 100 pF
# input caps and undo their dry-electrode CMRR margin.
NC_PINS = {p for p, n in PINS.items() if n == "AGND"}
SHIELD_NET = "REF"
NETS = ["", "REF", "CH1P", "CH1N", "CH2P", "CH2N", "CH3P", "CH3N"]
NET = {n: i for i, n in enumerate(NETS)}
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        "Forehead EMG electrode flex. Generated by gen_flex.py: edit there, not here.",
        f"Tail runs along the subject's {'right' if TAIL_SIDE == 'R' else 'left'} to main board J6 (pin order from hardware/emg-rev-a-kicad c72bb90).",
        "CH1 frontalis (brow raise), CH2 corrugator (frown), CH3 anterior temporalis (jaw clench).",
        "REF is the shared RLD electrode; the three REF pins all land on it. Main board AGND pins 1/5/9 are not connected; the B.Cu hatched shield is tied to REF.",
        "Electrode pairs: 20 mm centre spacing along the fibres (corrugator 15 mm).",
    ]
    for k, t in enumerate(notes):
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

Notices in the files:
parts and their libraries:
Espressif ESP32-S3-MINI-1, from the CERN KiCad library (CERN-OHL-P-2.0, (c) CERN) via PartReel. Centre GND pads 66-73 renumbered to 65 to join the symbol EP pin; courtyard trimmed to the module; antenna keepout kept.
